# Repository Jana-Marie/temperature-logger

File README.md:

# temperature-logger

Anotter USB temperature logger that can record up to four channels with thermocouple or NTCs connected via CDC directly or SCPI to USB. You can choose how you want to receive the data by moving the selector switch next to the Type-C receptacle. If you switch to CSV, it will simply output all connected channels to your console in a machine and human readable format (CSV or TSV, I prefer TSV) at about 10 readings per second. If you switch to SCPI, an SCPI terminal is displayed via USB so that you can integrate the logger into your lab equipment. This is particularly handy because you can also use it to control the OC- or H-Bridge outputs, which turns the logger into a thermal IO card. This can be useful when working with Peltier- and heating elements.

Having needed a temperature logger several times in the past, after hacking two together for spontaneous testing, I decided to develop a proper one. This is my result. :3

### Inputs

Each of the four inputs can either be configured as thermocouple or NTC (resistance measuring) input. At the moment they are assembly options, I need to test if I can assmble both at the same time.

**thermocouple**

One MAX31855KASA can be populated per channel, enabling the reading of K-type thermocouples. Other versions of this IC are available if other thermocouple types are required.

**NTC**

The NTC amplifier is based on [this appnote](https://www.ti.com/lit/an/sboa323a/sboa323a.pdf) and allows amplification of small ranges to the full ADC range. This was an important motivation for this project as I needed a multi-channel body temperature logger.

If you want to know more, you can check out the [schematic](https://github.com/Jana-Marie/temperature-logger/blob/main/temperature-logger.pdf).

### TODO

 - [ ] implement SCPI - done in the SCPI branch, check it out, but there is not much space left on the STM32, hence no merge yet
 - [ ] add sigrok communication/protocol 

### License

Copyright Jana Marie Hemsing 2023.

This source describes Open Hardware and is licensed under the CERN-OHL-S v2.

You may redistribute and modify this source and make products using it under
the terms of the CERN-OHL-S v2 (https://ohwr.org/cern_ohl_s_v2.txt).

This source is distributed WITHOUT ANY EXPRESS OR IMPLIED WARRANTY,
INCLUDING OF MERCHANTABILITY, SATISFACTORY QUALITY AND FITNESS FOR A
PARTICULAR PURPOSE. Please see the CERN-OHL-S v2 for applicable conditions.

Source location: https://github.com/Jana-Marie/temperature-logger

As per CERN-OHL-S v2 section 4, should You produce hardware based on this
source, You must where practicable maintain the Source Location visible
on the external case of the Gizmo or other products you make using this
source.

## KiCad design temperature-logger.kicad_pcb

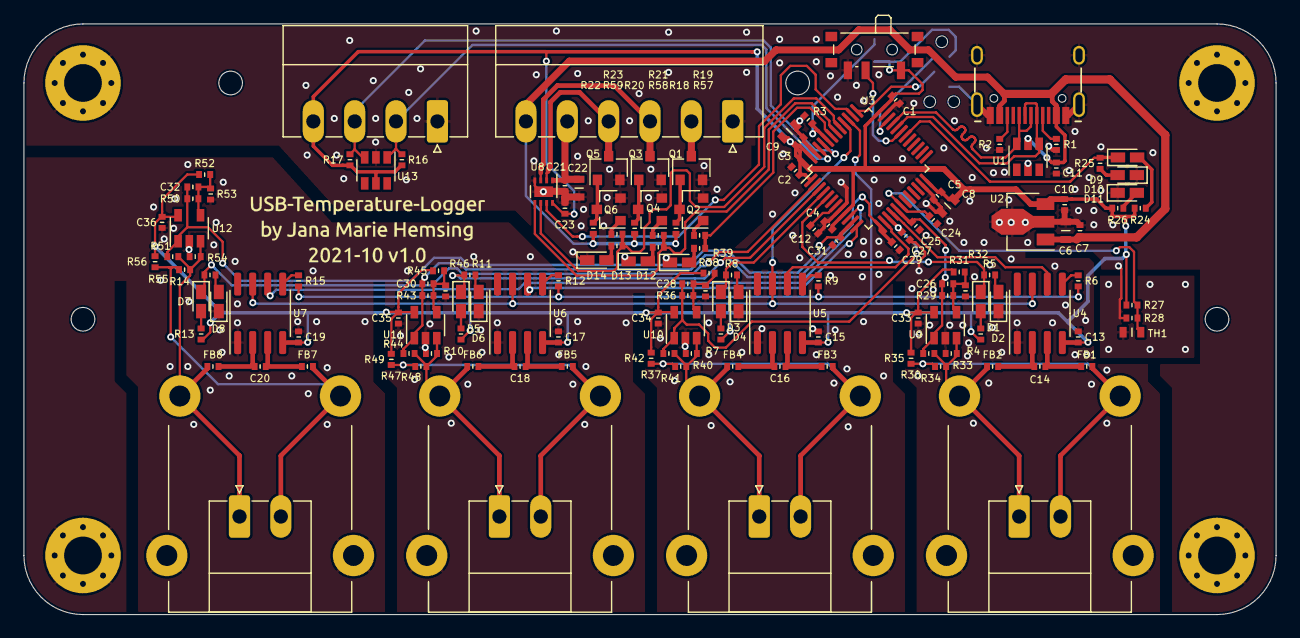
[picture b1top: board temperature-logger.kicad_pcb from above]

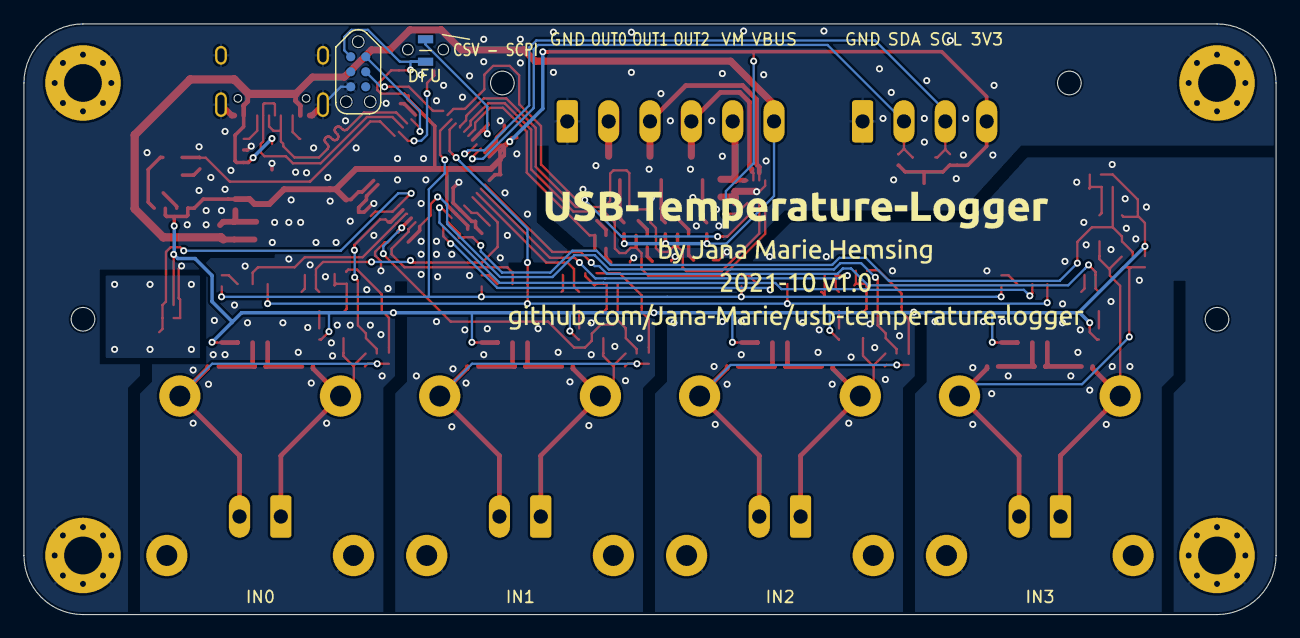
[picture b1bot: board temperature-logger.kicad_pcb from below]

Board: 4 copper layers, 106.0 x 50.0 mm, 155 parts (2 on the bottom side), 82 nets.

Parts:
C1, C2, C3, C4, C5, C7, C10, C11, C12, C13, C15, C17, C19, C24: 100n; C_0402
C6, C8, C9: 1uF; C_0603
C14, C16, C18, C20, C26, C28, C30, C32: 10n; C_0402
C21, C23, C25, C27, C29, C31, C33, C34, C35, C36: DNP; C_0402
C22: DNP; C_0603
D1, D3, D5, D7, D9: RED; LED_0603_1608Metric
D2, D4, D6, D8, D10, D12, D13, D14: GREEN; LED_0603_1608Metric
D11: BLUE; LED_0603_1608Metric
FB1, FB2, FB3, FB4, FB5, FB6, FB7, FB8: FERRET; L_0402
H1, H2, H3, H4: M3; MountingHole_3.2mm_M3_Pad_Via
J1: USB; USB-C 16Pin
J2, J3, J4, J5: THERMOCOUPLE; PCC-SMP
J6: OUT; PhoenixContact_MC_1,5_6-G-3.5_1x06_P3.50mm_Horizontal
J7: I2C; PhoenixContact_MC_1,5_4-G-3.5_1x04_P3.50mm_Horizontal
J8, J9, J10, J11: DNP; PhoenixContact_MC_1,5_2-G-3.5_1x02_P3.50mm_Horizontal
JP1: DFU; R_0805
P1: TC2030
Q1, Q3, Q5: 2N7002; SOT-23
Q2, Q4, Q6: BC817; SOT-23
R1, R2, R3, R16, R17, R27, R28: 5k1; R_0402
R4, R5, R7, R8, R10, R11, R13, R14, R18, R19, R20, R21, R22, R23, R24, R25, R26, R57, R58, R59: 220; R_0402
R6, R9, R12, R15: 10; R_0402
R29, R30, R31, R32, R33, R34, R35, R36, R37, R38, R39, R40, R41, R42, R43, R44, R45, R46, R47, R48, R49, R50, R51, R52, R53, R54, R55, R56: DNP; R_0402
SW1: SCPI_CSV; SW_SPDT_PCM12
TH1: NTC; R_0603
U1, U13: USBLC6-4; SOT-23-6
U2: AP2204R-3.3; SOT-89-3
U3: STM32F072C8Tx; LQFP-48_7x7mm_P0.5mm
U4, U5, U6, U7: MAX31855KASA; SOIC-8_3.9x4.9mm_P1.27mm
U8: DRV8837; WSON-8-1EP_2x2mm_P0.5mm_EP0.9x1.6mm
U9, U10, U11, U12: TLV9001; SOT-23-5

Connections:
+3V3: C1.2, C2.2, C3.2, C4.2, C5.2, C8.2, C9.2, C10.2, C13.2, C15.2, C17.2, C19.2, C23.2, C33.2, C34.2, C35.2, C36.2, J7.4, JP1.2, P1.1 (VCC), R4.1, R7.1, R10.1, R13.1, R16.1, R17.2, R24.1, R26.1, R27.1, R31.1, R35.1, R38.1, R42.1, R45.1, R49.1, R52.1, R56.1, SW1.1 (A), U2.3 (VOUT), U3.1 (VBAT), U3.9 (VDDA), U3.24 (VDD), U3.36 (VDDIO2), U3.48 (VDD), U4.4 (VCC), U5.4 (VCC), U6.4 (VCC), U7.4 (VCC), U8.8 (VCC), U9.5 (V+), U10.5 (V+), U11.5 (V+), U12.5 (V+), U13.5 (VBUS)
CIPO: U3.40 (PB4), U4.7 (SO), U5.7 (SO), U6.7 (SO), U7.7 (SO)
CS0: U3.16 (PA6), U4.6 (~CS)
CS1: U3.14 (PA4), U5.6 (~CS)
CS2: U3.12 (PA2), U6.6 (~CS)
CS3: U3.10 (PA0), U7.6 (~CS)
D+: J1.A6 (D+), J1.B6 (D+), U1.6 (IO4), U3.33 (PA12)
D-: J1.A7 (D-), J1.B7 (D-), U1.4 (IO3), U3.32 (PA11)
GND: C1.1, C2.1, C3.1, C4.1, C5.1, C6.1, C7.1, C8.1, C9.1, C10.1, C11.1, C12.1, C13.1, C15.1, C17.1, C19.1, C21.1, C22.1, C23.1, C24.1, C25.1, C27.1, C29.1, C31.1, C33.1, C34.1, C35.1, C36.1, D2.1 (K), D4.1 (K), D6.1 (K), D8.1 (K), D10.1 (K), D11.1 (K), D12.1 (K), D13.1 (K), D14.1 (K), H1.1, H2.1, H3.1, H4.1, J1.A1 (GND), J1.A12 (GND), J1.B1 (GND), J1.B12 (GND), J1.S1 (SHIELD), J2.MP (MountPin), J3.MP (MountPin), J4.MP (MountPin), J5.MP (MountPin), J6.1, J7.1, P1.5 (GND), Q1.2 (S), Q2.2 (E), Q3.2 (S), Q4.2 (E), Q5.2 (S), Q6.2 (E), R1.1, R2.2, R3.1, R28.2, R32.2, R33.2, R39.2, R40.2, R46.2, R47.2, R53.2, R54.2, SW1.3 (C), TH1.2, U1.2 (GND), U2.2 (GND), U3.8 (VSSA), U3.23 (VSS), U3.35 (VSS), U3.47 (VSS), U4.1 (GND), U5.1 (GND), U6.1 (GND), U7.1 (GND), U8.4 (GND), U8.9 (GND), U9.2 (V-), U10.2 (V-), U11.2 (V-), U12.2 (V-), U13.2 (GND)
LED0: D1.1 (K), R5.2, U3.5 (PF0)
LED1: D3.1 (K), R8.2, U3.4 (PC15)
LED2: D5.1 (K), R11.2, U3.3 (PC14)
LED3: D7.1 (K), R14.2, U3.2 (PC13)
NTC0: C25.2, C26.1, R29.1, R30.1, U3.17 (PA7), U9.1
NTC1: C27.2, C28.1, R36.1, R37.1, U3.15 (PA5), U10.1
NTC2: C29.2, C30.1, R43.1, R44.1, U3.13 (PA3), U11.1
NTC3: C31.2, C32.1, R50.1, R51.1, U3.11 (PA1), U12.1
NTC_BOARD: C24.2, R27.2, R28.1, TH1.1, U3.18 (PB0)
unnamed: C12.2, U3.7 (NRST)
unnamed: C14.1, FB1.2, U4.3 (T+)
unnamed: C14.2, FB2.2, U4.2 (T-)
unnamed: C16.1, FB3.2, U5.3 (T+)
unnamed: C16.2, FB4.2, U5.2 (T-)
unnamed: C18.1, FB5.2, U6.3 (T+)
unnamed: C18.2, FB6.2, U6.2 (T-)
unnamed: C20.1, FB7.2, U7.3 (T+)
unnamed: C20.2, FB8.2, U7.2 (T-)
unnamed: C26.2, R29.2, R31.2, R32.1, U9.4 (-)
unnamed: C28.2, R36.2, R38.2, R39.1, U10.4 (-)
unnamed: C30.2, R43.2, R45.2, R46.1, U11.4 (-)
unnamed: C32.2, R50.2, R52.2, R53.1, U12.4 (-)
unnamed: D1.2 (A), R4.2
unnamed: D2.2 (A), R5.1
unnamed: D3.2 (A), R7.2
unnamed: D4.2 (A), R8.1
unnamed: D5.2 (A), R10.2
unnamed: D6.2 (A), R11.1
unnamed: D7.2 (A), R13.2
unnamed: D8.2 (A), R14.1
unnamed: D9.2 (A), R24.2
unnamed: D10.2 (A), R25.1
unnamed: D11.2 (A), R26.2
unnamed: D12.2 (A), R57.1
unnamed: D13.2 (A), R58.1
unnamed: D14.2 (A), R59.1
unnamed: FB1.1, J2.1, J8.2, R34.1, R35.2
unnamed: FB2.1, J2.2, J8.1, R30.2, R33.1, R34.2, U9.3 (+)
unnamed: FB3.1, J3.1, J9.2, R41.1, R42.2
unnamed: FB4.1, J3.2, J9.1, R37.2, R40.1, R41.2, U10.3 (+)
unnamed: FB5.1, J4.1, J10.2, R48.1, R49.2
unnamed: FB6.1, J4.2, J10.1, R44.2, R47.1, R48.2, U11.3 (+)
unnamed: FB7.1, J5.1, J11.2, R55.1, R56.2
unnamed: FB8.1, J5.2, J11.1, R51.2, R54.1, R55.2, U12.3 (+)
unnamed: J1.A5 (CC1), R1.2
unnamed: J1.B5 (CC2), R2.1
unnamed: J6.2, Q1.3 (D)
unnamed: J6.3, Q3.3 (D), U8.3 (OUT2)
unnamed: J6.4, Q5.3 (D), U8.2 (OUT1)
unnamed: JP1.1, R3.2, U3.44 (BOOT0)
unnamed: Q1.1 (G), Q2.3 (C), R18.1
unnamed: Q2.1 (B), R19.1
unnamed: Q3.1 (G), Q4.3 (C), R20.1
unnamed: Q4.1 (B), R21.1
unnamed: Q5.1 (G), Q6.3 (C), R22.1
unnamed: Q6.1 (B), R23.1
unnamed: R6.2, U4.5 (SCK)
unnamed: R9.2, U5.5 (SCK)
unnamed: R12.2, U6.5 (SCK)
unnamed: R15.2, U7.5 (SCK)
OUT0: R23.2, R59.2, U3.41 (PB5), U8.6 (IN1)
OUT1: R21.2, R58.2, U3.42 (PB6), U8.5 (IN2)
OUT2: R19.2, R57.2, U3.43 (PB7)
OUT_nSLEEP: U3.38 (PA15), U8.7 (~SLEEP)
SCK: R6.1, R9.1, R12.1, R15.1, U3.39 (PB3)
SCL: J7.3, R17.1, U3.45 (PB8), U13.3 (IO2)
SDA: J7.2, R16.2, U3.46 (PB9), U13.1 (IO1)
STATUS_LED: D9.1 (K), R25.2, U3.30 (PA9)
SWCLK: P1.4 (SWCLK/TCK), U3.37 (PA14)
SWDIO: P1.2 (SWDIO/TMS), U3.34 (PA13)
SW_SCPI_CSV: SW1.2 (B), U3.31 (PA10)
VBUS: C6.2, C7.2, C11.2, J1.A4 (VBUS), J1.A9 (VBUS), J1.B4 (VBUS), J1.B9 (VBUS), J6.6, R18.2, R20.2, R22.2, U1.5 (VBUS), U2.1 (VIN)
VM: C21.2, C22.2, J6.5, U8.1 (VM)

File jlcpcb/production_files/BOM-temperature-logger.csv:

Comment,Designator,Footprint,LCSC
USBLC6-4,"U1,U13",SOT-23-6,C111212
10n,"C14,C16,C18,C20,C26,C28,C30,C32",C_0402,C15195
100n,"C1,C10,C11,C12,C13,C15,C17,C19,C2,C24,C3,C4,C5,C7",C_0402,C1525
AP2204R-3.3,U2,SOT-89-3,C156303
1uF,"C6,C8,C9",C_0603,C15849
USB,J1,USB-C 16Pin,C165948
SCPI_CSV,SW1,SW_SPDT_PCM12,C221841
RED,"D1,D3,D5,D7,D9",LED_0603_1608Metric,C2286
220,"R10,R11,R13,R14,R18,R19,R20,R21,R22,R23,R24,R25,R26,R4,R5,R57,R58,R59,R7,R8",R_0402,C25091
10,"R12,R15,R6,R9",R_0402,C25123
5k1,"R1,R16,R17,R2,R27,R28,R3",R_0402,C25905
MAX31855KASA,"U4,U5,U6,U7",SOIC-8_3.9x4.9mm_P1.27mm,C52028
BC817,"Q2,Q4,Q6",SOT-23,C52801
BLUE,D11,LED_0603_1608Metric,C72041
GREEN,"D10,D12,D13,D14,D2,D4,D6,D8",LED_0603_1608Metric,C72043
STM32F072C8Tx,U3,LQFP-48_7x7mm_P0.5mm,C80488
2N7002,"Q1,Q3,Q5",SOT-23,C8545
FERRET,"FB1,FB2,FB3,FB4,FB5,FB6,FB7,FB8",L_0402,C87551
THERMOCOUPLE,J2,PCC-SMP,
THERMOCOUPLE,J3,PCC-SMP,
THERMOCOUPLE,J4,PCC-SMP,
THERMOCOUPLE,J5,PCC-SMP,
OUT,J6,"PhoenixContact_MC_1,5_6-G-3.5_1x06_P3.50mm_Horizontal",
I2C,J7,"PhoenixContact_MC_1,5_4-G-3.5_1x04_P3.50mm_Horizontal",
DNP,J8,"PhoenixContact_MC_1,5_2-G-3.5_1x02_P3.50mm_Horizontal",
DNP,J9,"PhoenixContact_MC_1,5_2-G-3.5_1x02_P3.50mm_Horizontal",
DNP,J10,"PhoenixContact_MC_1,5_2-G-3.5_1x02_P3.50mm_Horizontal",
DNP,J11,"PhoenixContact_MC_1,5_2-G-3.5_1x02_P3.50mm_Horizontal",
NTC,TH1,R_0603,
TLV9001,U9,SOT-23-5,
TLV9001,U10,SOT-23-5,
TLV9001,U11,SOT-23-5,
DRV8837,U8,WSON-8-1EP_2x2mm_P0.5mm_EP0.9x1.6mm,
TLV9001,U12,SOT-23-5,
DFU,JP1,R_0805,

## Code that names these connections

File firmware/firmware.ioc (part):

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Mcu.Name=STM32F072C(8-B)Tx
Mcu.Package=LQFP48
Mcu.UserName=STM32F072C8Tx
PA0.GPIOParameters=GPIO_Label
PA0.GPIO_Label=NSS3
PA0.Signal=GPIO_Output
PA1.GPIOParameters=GPIO_Label
PA1.GPIO_Label=NTC3
PA1.Mode=IN1
PA1.Signal=ADC_IN1
PA10.GPIOParameters=GPIO_Label
PA10.GPIO_Label=SW_SCPI_CSV
PA10.Signal=GPIO_Input
PA11.Mode=Device
PA11.Signal=USB_DM
PA12.Mode=Device
PA12.Signal=USB_DP
PA13.Mode=Serial_Wire
PA13.Signal=SYS_SWDIO
PA14.Mode=Serial_Wire
PA14.Signal=SYS_SWCLK
PA15.GPIOParameters=GPIO_Label
PA15.GPIO_Label=OUT_nSLEEP
PA15.Signal=GPIO_Output
PA2.GPIOParameters=GPIO_Label
PA2.GPIO_Label=NSS2
PA2.Signal=GPIO_Output
PA3.GPIOParameters=GPIO_Label
PA3.GPIO_Label=NTC2
PA3.Mode=IN3
PA3.Signal=ADC_IN3
PA4.GPIOParameters=GPIO_Label
PA4.GPIO_Label=NSS1
PA4.Signal=GPIO_Output
PA5.GPIOParameters=GPIO_Label
PA5.GPIO_Label=NTC1
PA5.Mode=IN5
PA5.Signal=ADC_IN5
PA6.GPIOParameters=GPIO_Label
PA6.GPIO_Label=NSS0
PA6.Signal=GPIO_Output
PA7.GPIOParameters=GPIO_Label
PA7.GPIO_Label=NTC0
PA7.Mode=IN7
PA7.Signal=ADC_IN7
PA9.GPIOParameters=GPIO_Label
PA9.GPIO_Label=LED_STATUS
PA9.Signal=GPIO_Output
PB0.GPIOParameters=GPIO_Label
PB0.GPIO_Label=NTC_BOARD
PB0.Mode=IN8
PB0.Signal=ADC_IN8
PB3.Mode=RX_Only_Simplex_Unidirect_Master
PB3.Signal=SPI1_SCK
PB4.Mode=RX_Only_Simplex_Unidirect_Master
PB4.Signal=SPI1_MISO
PB5.GPIOParameters=GPIO_Label
PB5.GPIO_Label=OUT0
PB5.Signal=GPIO_Output
PB6.GPIOParameters=GPIO_Label
PB6.GPIO_Label=OUT1
PB6.Signal=GPIO_Output
PB7.GPIOParameters=GPIO_Label
PB7.GPIO_Label=OUT2
PB7.Signal=GPIO_Output
PB8.Mode=I2C
PB8.Signal=I2C1_SCL
PB9.Mode=I2C
PB9.Signal=I2C1_SDA
PC13.GPIOParameters=GPIO_Label
PC13.GPIO_Label=LED3
PC13.Signal=GPIO_Output
PC14-OSC32_IN.GPIOParameters=GPIO_Label
PC14-OSC32_IN.GPIO_Label=LED2
PC14-OSC32_IN.Signal=GPIO_Output
PC15-OSC32_OUT.GPIOParameters=GPIO_Label
PC15-OSC32_OUT.GPIO_Label=LED1
PC15-OSC32_OUT.Signal=GPIO_Output
PF0-OSC_IN.GPIOParameters=GPIO_Label
PF0-OSC_IN.GPIO_Label=LED0
PF0-OSC_IN.Signal=GPIO_Output
RCC.SYSCLKFreq_VALUE=48000000
RCC.SYSCLKSource=RCC_SYSCLKSOURCE_HSI48
board=custom

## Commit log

2021-10-18 exported gerbers
2021-10-18 added pdf
2021-12-02 added fw
2021-12-02 added openocd cfg
2021-12-03 added HW files
2021-12-03 added 3d files
2022-01-19 added schematic pdf
2022-01-19 updated to kicad 6
2022-01-19 updated blind to kicad 6
2022-01-19 added gitignore
2022-01-19 removed build
2022-01-19 updated gitignore
2022-01-19 added four thermocouple readout, needs much wore work
2022-01-19 added license
2022-01-19 added images
2022-03-01 fixed isses #1
2022-03-01 udated gerber
2022-03-03 all channels will be reported, LEDs now show connection status
2022-03-07 fixed led bug
2022-03-07 added todos
2022-03-08 added scpi
2023-06-05 added jlcpcb plugin mappings
